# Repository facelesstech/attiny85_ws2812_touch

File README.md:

# attiny85_ws2812_touch
attiny85_ws2812_touch
* [Blog post](https://facelesstech.wordpress.com/2023/09/17/gameboy-macro-rgb-light-bar/)

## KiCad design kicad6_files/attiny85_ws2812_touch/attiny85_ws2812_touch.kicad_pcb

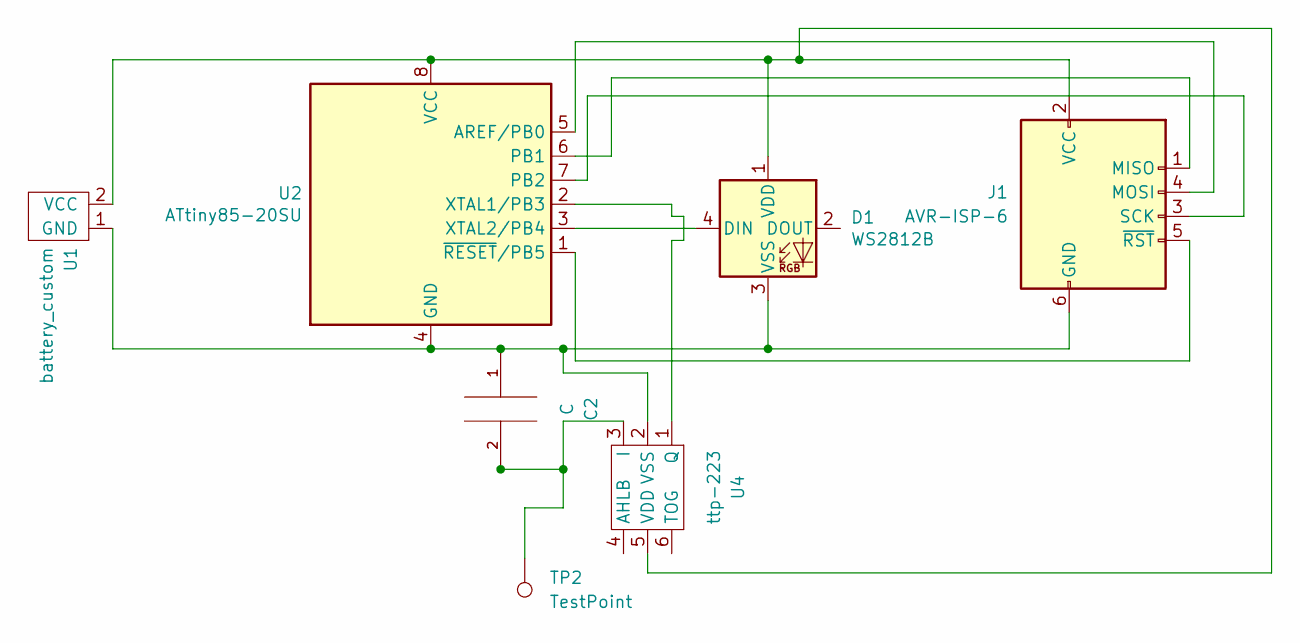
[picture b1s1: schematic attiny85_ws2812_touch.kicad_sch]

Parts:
C2: C; C_0603_1608Metric_Pad1.08x0.95mm_HandSolder
D1: WS2812B; ws2812_header_custom_strip_oval
J1: AVR-ISP-6; ISP_6pin_small_custom
TP2: TestPoint; 1mm_test_point
U1: battery_custom; vcc_gnd_2pin_custom_thin
U2: ATtiny85-20SU; attiny85_arduino
U4: ttp-223; SOT-23-6_Handsoldering

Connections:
unnamed: D1.4 (DIN), U2.3 (XTAL2/PB4)
unnamed: D1.1 (VDD), J1.2 (VCC), U1.2 (VCC), U2.8 (VCC), U4.5 (VDD)
unnamed: C2.1, D1.3 (VSS), J1.6 (GND), U1.1 (GND), U2.4 (GND), U4.2 (VSS)
unnamed: J1.1 (MISO), U2.6 (PB1)
unnamed: J1.4 (MOSI), U2.5 (AREF/PB0)
unnamed: J1.3 (SCK), U2.7 (PB2)
unnamed: J1.5 (~RST), U2.1 (~RESET/PB5)
unnamed: U2.2 (XTAL1/PB3), U4.1 (Q)
unnamed: C2.2, TP2.1, U4.3 (I)

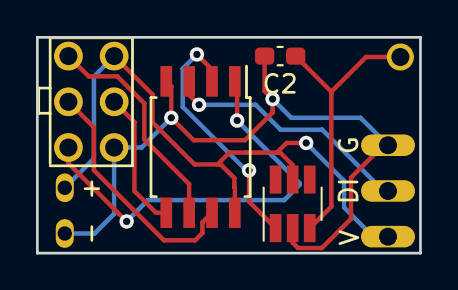
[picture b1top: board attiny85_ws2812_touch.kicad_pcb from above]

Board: 2 copper layers, 21.3 x 12.0 mm, 7 parts (0 on the bottom side), 9 nets.

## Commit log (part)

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2023-09-15 added the 3d printing files
2023-09-15 added kicad files
2023-09-15 added photo
2023-09-15 added blog post link
2023-09-17 added arduino code
2023-10-14 edited the readme
2023-10-14 removed photo
